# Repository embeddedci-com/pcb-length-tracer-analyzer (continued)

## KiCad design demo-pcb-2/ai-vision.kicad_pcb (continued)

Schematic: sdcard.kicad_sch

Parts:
C180: 100n; C_0402_1005Metric; LCSC C307331
C181: 4.7u; C_0805_2012Metric; LCSC C1779
Card1: TF PUSH; C393941_TF-SMD_TF-PUSH; LCSC C393941
D4, D5: PESD3V3L4UG,115; C70500_SOT-353_L2_0-W1_2-P0_65-LS2_1-TL; LCSC C70500
R101: 10k; R_0402_1005Metric; LCSC C25744
R102, R104, R105, R106, R107: 47k; R_0402_1005Metric; LCSC C25792
R103: 22; R_0402_1005Metric; LCSC C25092
R108: 0; R_0402_1005Metric; LCSC C17168

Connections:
/MP257/SDMMC1_CK: D4.1 (C1), R101.2, R103.1; also elsewhere on the board
/MP257/SDMMC1_CMD: Card1.3 (CMD), D5.5 (C4), R105.2; also elsewhere on the board
/MP257/SDMMC1_D0: Card1.7 (DAT0), D4.3 (C2), R106.2; also elsewhere on the board
/MP257/SDMMC1_D1: Card1.8 (DAT1), D4.5 (C4), R107.2; also elsewhere on the board
/MP257/SDMMC1_D2: Card1.1 (DAT2), D5.1 (C1), R102.2; also elsewhere on the board
/MP257/SDMMC1_D3: Card1.2 (CD/DAT3), D5.3 (C2), R104.2; also elsewhere on the board
/MP257/uSD_DETECT: R108.1; also elsewhere on the board
GND: C180.2, C181.2, Card1.6 (VSS), Card1.10, Card1.11, Card1.12, Card1.13, D4.2 (CA), D5.2 (CA); also elsewhere on the board
unnamed: Card1.5 (CLX), R103.2
unnamed: Card1.CD, R108.2
VDDIO_SDCARD: C180.1, R101.1, R102.1, R104.1, R105.1, R106.1, R107.1; also elsewhere on the board
VDD_SDCARD: C181.1, Card1.4 (VDD); also elsewhere on the board

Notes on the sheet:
(input with pull up)
22 ohms to place near MPU

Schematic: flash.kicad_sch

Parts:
C179: 100n; C_0402_1005Metric; LCSC C307331
R100: 10k; R_0402_1005Metric; LCSC C25744
U10: W25Q64JVSSIQ_C179171; C179171_SOIC-8_L5_3-W5_3-P1_27-LS8_0-BL; LCSC C179171

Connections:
+3V3: C179.1, R100.1, U10.8 (VCC); also elsewhere on the board
/MP257/flash_clk: U10.6 (CLK); also elsewhere on the board
/MP257/flash_cs: R100.2, U10.1 (CS#); also elsewhere on the board
/MP257/flash_io0: U10.5 (DI(IO0)); also elsewhere on the board
/MP257/flash_io1: U10.2 (DO(IO1)); also elsewhere on the board
/MP257/flash_io2: U10.3 (WP#(IO2)); also elsewhere on the board
/MP257/flash_io3: U10.7 (HOLD#orRESET#(IO3)); also elsewhere on the board
GND: C179.2, U10.4 (GND); also elsewhere on the board

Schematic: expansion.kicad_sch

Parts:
C182, C183, C184, C185, C186, C187, C188, C189, C190, C191, C193, C194, C196: 100n; C_0402_1005Metric; LCSC C307331
C192, C195: 10u; C_0603_1608Metric; LCSC C96446
H5: MountingHole; MountingHole_2.5mm
Q1: SI2302_C427390; C427390_SOT-23-3_L2_9-W1_3-P1_90-LS2_4-BR; LCSC C427390
R109, R110: 200; R_0402_1005Metric; LCSC C25087
R111, R112, R118, R119: 49.9; R_0402_1005Metric; LCSC C25120
R113: 10k; R_0402_1005Metric; LCSC C25744
R114, R115, R116, R117: 0; R_0402_1005Metric; LCSC C17168
R120, R121: 0; R_0402_1005Metric; LCSC C17168; not fitted
U3: STM32MP257DAI3; C39969643_TFBGA-436_L18_0-W18_0-0_80-TL_STM32MP257FAI3; PART_TYPE IC; LCSC C39969643
U11: DSC557-0344FI0_C1669965; C1669965_QFN-14_L3_2-W2_5-P0_50-BL-EP; LCSC C1669965
U12: MLD-NGFF-M-4.8H; C52766533_CONN-SMD_MLD-NGFF-M-4_8H; LCSC C52766533

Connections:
+3V3: C186.1, C187.1, C188.1, C189.1, C190.1, C191.1, C192.1, C193.1, C194.1, C195.1, C196.1, U12.2, U12.4, U12.12, U12.14, U12.16, U12.18, U12.70, U12.72, U12.74; also elsewhere on the board
/expansion/100MCLK0+: R114.2, U11.11 (CLK0+)
/expansion/100MCLK0-: R115.2, U11.10 (CLK0-)
/expansion/100MCLK1+: R117.2, U11.8 (CLK1+)
/expansion/100MCLK1-: R116.2, U11.9 (CLK1-)
/expansion/COMBOTX1+: C182.1, U3.AA19 (COMBOPHY_TX1P)
/expansion/COMBOTX1-: C183.1, U3.AB19 (COMBOPHY_TX1N)
/expansion/PCIE.CLKIN+: R112.1, R114.1, U3.Y18 (PCIE_CLKINP)
/expansion/PCIE.CLKIN-: R111.1, R115.1, U3.AA18 (PCIE_CLKINN)
/expansion/PCIE.CLKOUT+: R117.1, R118.1, R121.1, U12.55
/expansion/PCIE.CLKOUT-: R116.1, R119.1, R120.1, U12.53
/expansion/PCIE.CLKREQN: Q1.1 (G), R113.2, U12.52; also elsewhere on the board
/expansion/PCIE.NWAKE: U12.54; also elsewhere on the board
/expansion/PCIE.RSTN: U12.50; also elsewhere on the board
/expansion/PCIE.RX1+: U3.AA20 (COMBOPHY_RX1P), U12.43
/expansion/PCIE.RX1-: U3.AB20 (COMBOPHY_RX1N), U12.41
/expansion/PCIE.TX1+: C182.2, U12.49
/expansion/PCIE.TX1-: C183.2, U12.47
/expansion/PCIE_CLKOUT+: R121.2, U3.AA21 (PCIE_CLKOUTP)
/expansion/PCIE_CLKOUT-: R120.2, U3.AB21 (PCIE_CLKOUTN)
/expansion/USB_DATA+: U3.W17 (USB3DR_DP); also elsewhere on the board
/expansion/USB_DATA-: U3.Y17 (USB3DR_DM); also elsewhere on the board
GND: C184.2, C185.2, C186.2, C187.2, C188.2, C189.2, C190.2, C191.2, C192.2, C193.2, C194.2, C195.2, C196.2, Q1.2 (S), R109.2, R110.2, R111.2, R112.2, R118.2, R119.2, U11.4 (VSS), U11.15 (EP), U12.3, U12.9, U12.15, U12.27, U12.33, U12.39, U12.45, U12.51, U12.57, U12.71, U12.73, U12.76, U12.77; also elsewhere on the board
unnamed: Q1.3 (D), U11.1 (OE)
unnamed: R109.1, U3.Y20 (COMBOPHY_REXT)
unnamed: R110.1, U3.V17 (USB3DR_TXRTUNE)
VDDIO: C184.1, C185.1, R113.1, U11.12 (VDD1), U11.13 (VDD0); also elsewhere on the board

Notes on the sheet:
AC Cap : close to MP2
External 100Mhz
traces need to support 2.5A
Termination Resistor 49.9R CLK1 close to PCIe connector
49.9R CLK0 close to MP2

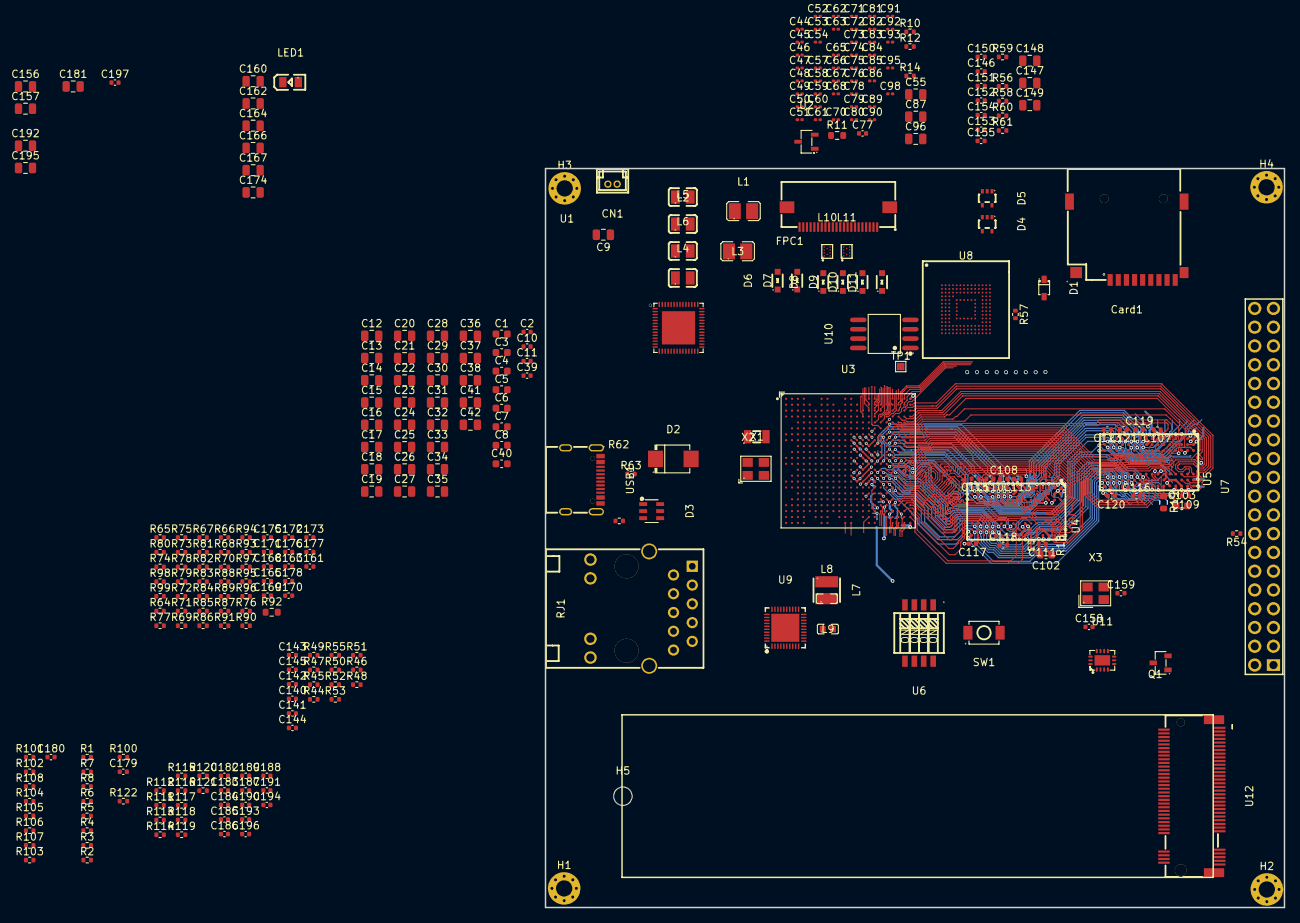
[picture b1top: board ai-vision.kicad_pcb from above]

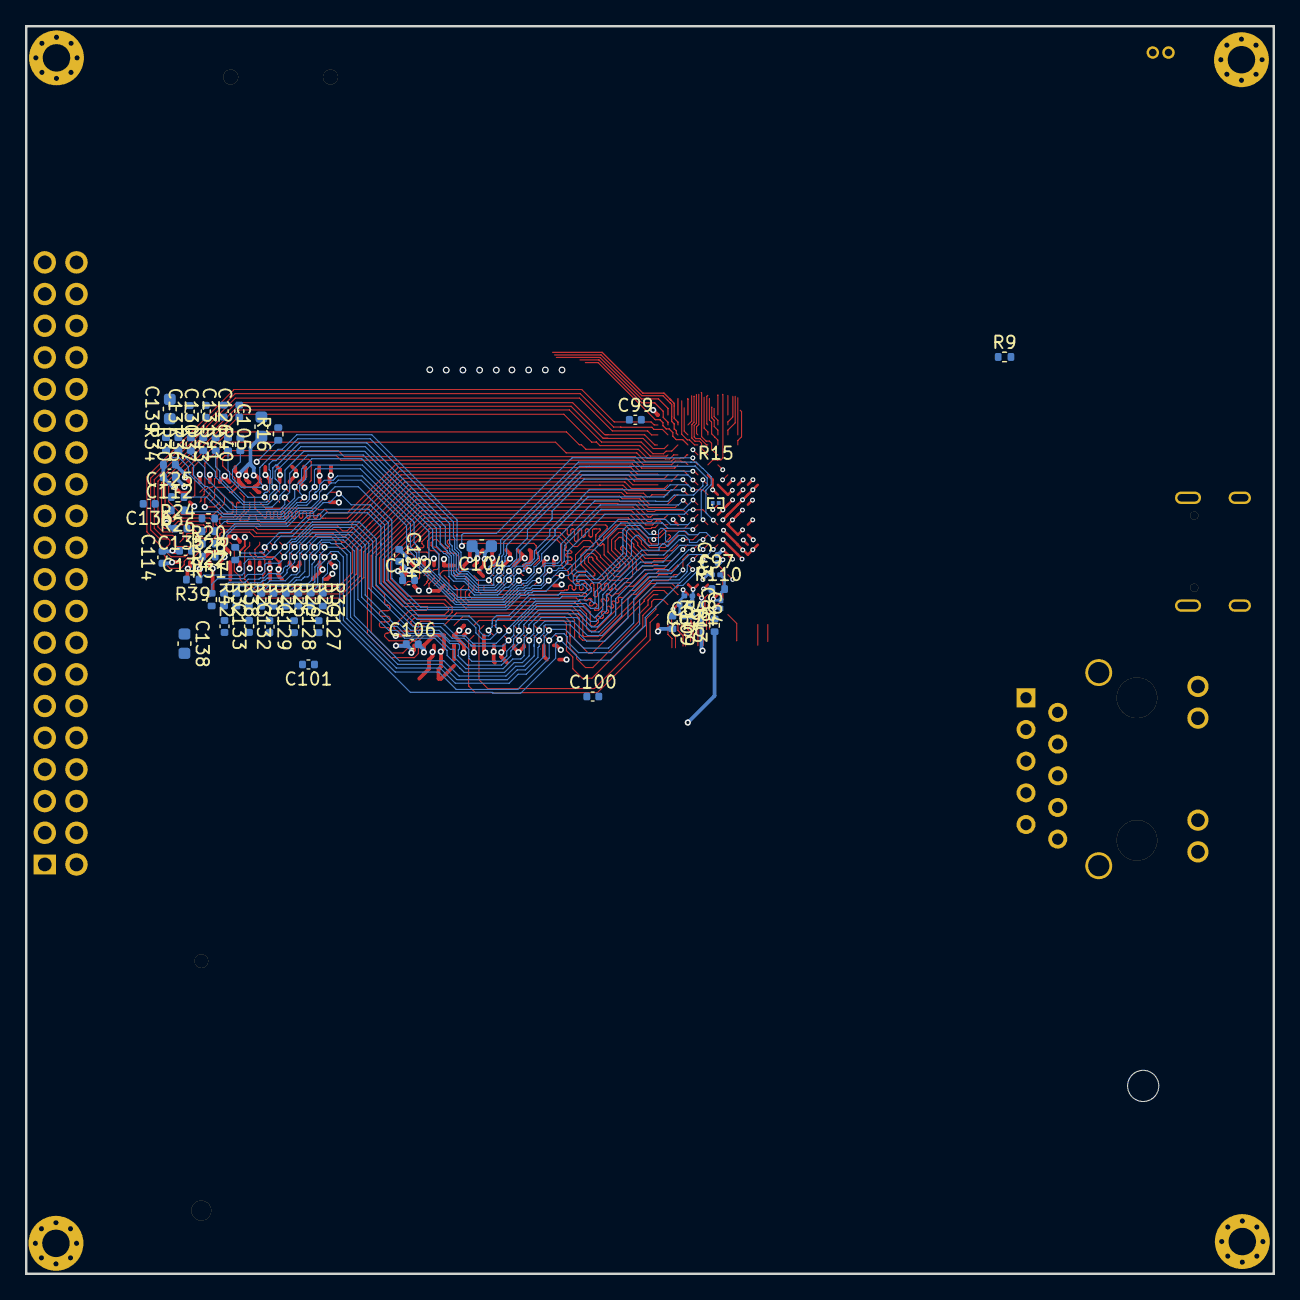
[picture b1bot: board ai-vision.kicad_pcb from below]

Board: 6 copper layers, 100.0 x 100.0 mm, 370 parts (63 on the bottom side), 303 nets.
